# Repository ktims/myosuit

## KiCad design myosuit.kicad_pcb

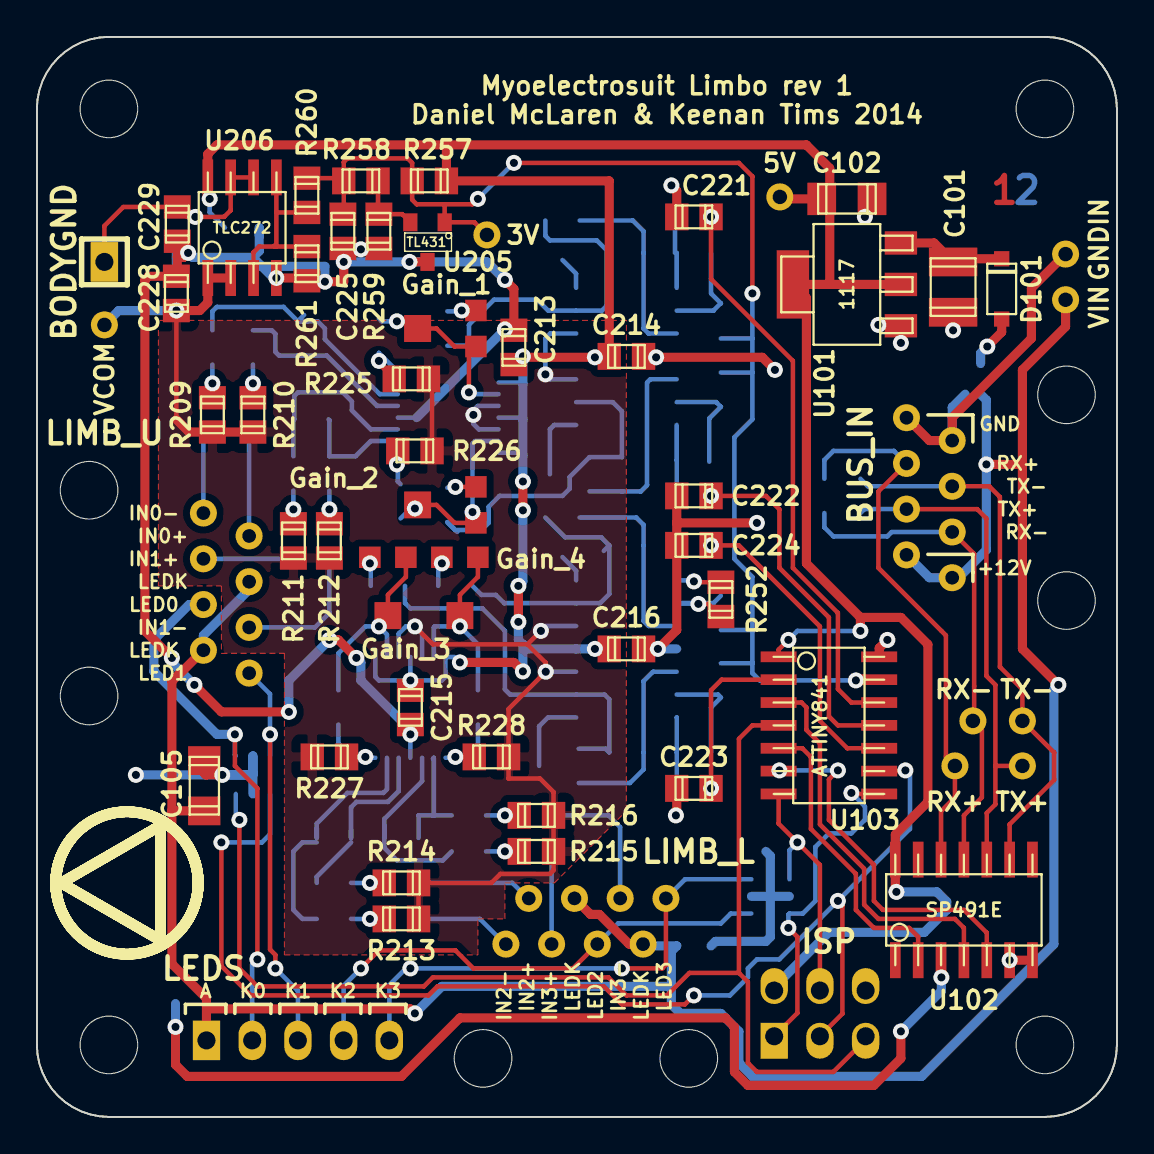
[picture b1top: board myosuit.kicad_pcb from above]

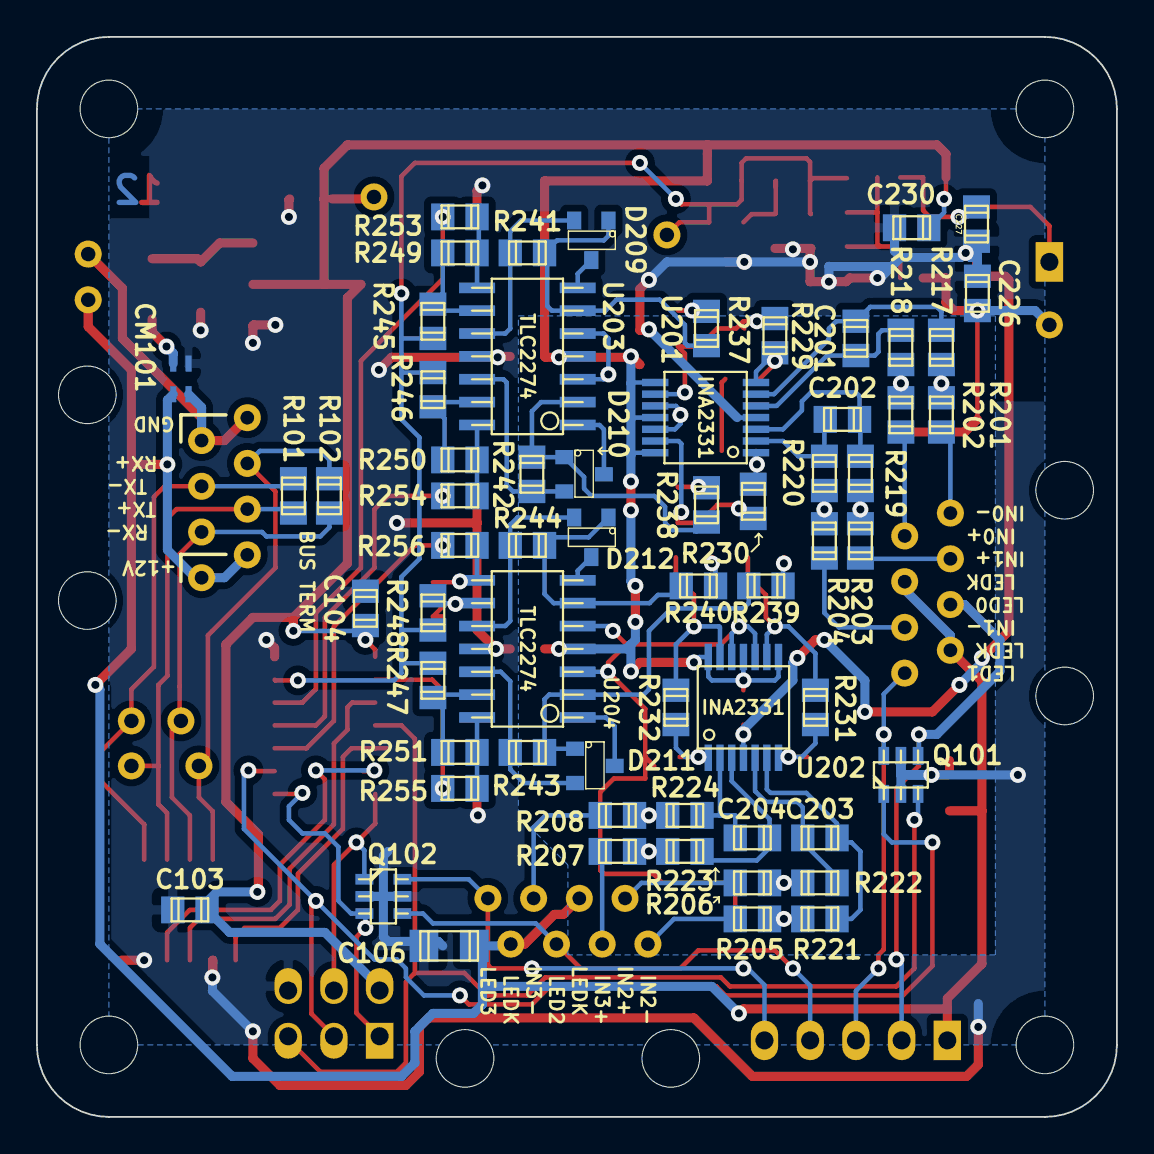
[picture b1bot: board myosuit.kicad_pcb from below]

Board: 2 copper layers, 60.0 x 60.0 mm, 123 parts (62 on the bottom side), 86 nets.

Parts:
C101: 47uF; c_1210
C102, C105, C106: 10uF; c_1206
C103, C104, C213, C214, C215, C216, C226, C227: 100nF; c_0805
C201, C202, C203, C204: 10nF; c_0805
C221, C222, C223, C224: 1u; c_0805
C225, C228, C229: 10u; c_0805
C230: 100n; c_0805
CM101: BOURNS-2012-CHOKE
D101: MBR0540; sod123
D209, D210, D211, D212: BAV199; SOT23
P101: LEDS; pin_strip_5-90
P102: ISP; pin_strip_3x2-90
P103: BUS_IN; FCI-shallow-rj45
P104: LIMB_U; FCI-shallow-rj45
P105: LIMB_L; FCI-shallow-rj45
P106: BODYGND; pin_strip_1
P107: VIN; Measurement_Point_Round-TH_Small
P108: GNDIN; Measurement_Point_Round-TH_Small
P109: TX+; Measurement_Point_Round-TH_Small
P110: 5V; Measurement_Point_Round-TH_Small
P111: RX+; Measurement_Point_Round-TH_Small
P112: RX-; Measurement_Point_Round-TH_Small
P113: TX-; Measurement_Point_Round-TH_Small
P201: 3V; Measurement_Point_Round-TH_Small
P202: VCOM; Measurement_Point_Round-TH_Small
Q101, Q102: FDC6305N; sot23-6
R101, R102: 120; r_0805
R201, R202, R203, R204, R205, R206, R207, R208, R217, R218, R219, R220, R221, R222, R223, R224, R258: 2k; r_0805
R209, R210, R211, R212, R213, R214, R215, R216: 3.3Meg; r_0805
R225, R226, R227, R228, R229, R230, R231, R232, R245, R246, R247, R248, R249, R250, R251, R252, R259: 10k; r_0805
R237, R238, R239, R240: 1k; r_0805
R241, R242, R243, R244, R260, R261: 100k; r_0805
R253, R254, R255, R256: 160; r_0805
R257: 330; r_0805
RV201: Gain_1; BOURNS-3303
RV202: Gain_2; BOURNS-3303
RV203: Gain_3; BOURNS-3303
RV204: Gain_4; BOURNS-3303
U101: 1117; sot223
U102: SP491E; so-14
U103: ATTINY841; so-14
U201, U202: INA2331; tssop-14
U203, U204: TLC2274; so-14
U205: TL431; SOT23
U206: TLC272; so-8
hole_3mm5, hole_3mm5#2, hole_3mm5#3, hole_3mm5#4: VAL**; hole_3mm5

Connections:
+3.3VADC: C225.1, P201.1, R245.1, R246.1, R247.1, R248.1, R257.2, R258.1, R260.1, U103.13, U205.1
+5V: C102.1, C103.1, C104.1, C213.2, C214.2, C215.2, C216.2, C230.2, P102.2, P110.1, R257.1, U101.2, U101.4, U102.14, U103.1, U201.8, U201.11, U201.14, U202.8, U202.11, U202.14, U203.4, U204.4, U206.8
/BUS_RX+: P103.6, P111.1, R102.2, U102.12
/BUS_RX-: P103.3, P112.1, R102.1, U102.11
/BUS_TX+: P103.4, P109.1, R101.1, U102.10
/BUS_TX-: P103.5, P113.1, R101.2, U102.9
/GNDIN: CM101.3, P103.7, P103.8, P108.1
/LED0: P101.2, P104.5, Q101.4
/LED1: P101.3, P104.8, Q101.6
/LED2: P101.4, P105.5, Q102.4
/LED3: P101.5, P105.8, Q102.6
/VIN: C105.1, C106.1, CM101.2, P101.1, P103.1, P103.2, P104.4, P104.7, P105.4, P105.7, P107.1
/analog input/BGND: C227.1, C229.1, P106.1, U206.6, U206.7
/analog input/IN0+: P104.2, R202.1
/analog input/IN0-: P104.1, R201.1
/analog input/IN1+: P104.3, R203.1
/analog input/IN1-: P104.6, R204.1
/analog input/IN2+: P105.2, R206.1
/analog input/IN2-: P105.1, R205.1
/analog input/IN3+: P105.3, R207.1
/analog input/IN3-: P105.6, R208.1
/analog input/OUT0: C221.1, R253.2, U103.12
/analog input/OUT1: C222.1, R254.2, U103.11
/analog input/OUT2: C223.1, R255.2, U103.2
/analog input/OUT3: C224.1, R256.2, U103.10
GND: C101.2, C102.2, C103.2, C104.2, C105.2, C106.2, C213.1, C214.1, C215.1, C216.1, C221.2, C222.2, C223.2, C224.2, C225.2, C226.2, C227.2, C228.2, C229.2, C230.1, CM101.4, P102.6, Q101.2, Q101.5, Q102.2, Q102.5, R259.2, R261.2, U101.1, U102.3, U102.6, U102.7, U103.14, U201.4, U202.4, U203.11, U204.11, U205.3, U206.4
unnamed: C101.1, D101.2, U101.3
unnamed: C201.1, R217.2, U201.6
unnamed: C201.2, R218.2, U201.5
unnamed: C202.1, R219.2, U201.3
unnamed: C202.2, R220.2, U201.2
unnamed: C203.1, R221.2, U202.6
unnamed: C203.2, R222.2, U202.5
unnamed: C204.1, R223.2, U202.3
unnamed: C204.2, R224.2, U202.2
unnamed: CM101.1, D101.1
unnamed: D209.1, R237.2, R241.1, U203.6
unnamed: D209.2, R241.2, U203.10
unnamed: D209.3, U203.7
unnamed: D210.1, R238.2, R242.1, U203.2
unnamed: D210.2, R242.2, U203.12
unnamed: D210.3, U203.1
unnamed: D211.1, R239.2, R243.1, U204.2
unnamed: D211.2, R243.2, U204.12
unnamed: D211.3, U204.1
unnamed: D212.1, R240.2, R244.1, U204.6
unnamed: D212.2, R244.2, U204.10
unnamed: D212.3, U204.7
unnamed: P102.1, Q102.3, U103.8
unnamed: P102.3, Q101.1, U103.9
unnamed: P102.4, Q102.1, U103.7
unnamed: P102.5, Q101.3, U103.4
unnamed: R201.2, R209.1, R217.1
unnamed: R202.2, R210.2, R218.1
unnamed: R203.2, R211.1, R219.1
unnamed: R204.2, R212.2, R220.1
unnamed: R205.2, R213.1, R221.1
unnamed: R206.2, R214.2, R222.1
unnamed: R207.2, R215.1, R223.1
unnamed: R208.2, R216.2, R224.1
unnamed: R225.2, R229.1, U201.7
unnamed: R226.2, R230.1, U201.1
unnamed: R227.2, R231.1, U202.7
unnamed: R228.2, R232.1, U202.1
unnamed: R229.2, RV201.1, RV201.2, U201.9
unnamed: R230.2, RV202.1, RV202.2, U201.13
unnamed: R231.2, RV203.1, RV203.2, U202.9
unnamed: R232.2, RV204.1, RV204.2, U202.13
unnamed: R237.1, RV201.3
unnamed: R238.1, RV202.3
unnamed: R239.1, RV203.3
unnamed: R240.1, RV204.3
unnamed: R245.2, R249.1, U203.9
unnamed: R246.2, R250.1, U203.13
unnamed: R247.2, R251.1, U204.13
unnamed: R248.2, R252.1, U204.9
unnamed: R249.2, R253.1, U203.8
unnamed: R250.2, R254.1, U203.14
unnamed: R251.2, R255.1, U204.14
unnamed: R252.2, R256.1, U204.8
unnamed: R258.2, R259.1, U205.2
unnamed: R260.2, R261.1, U206.3, U206.5
unnamed: U102.2, U103.5
unnamed: U102.4, U103.3
unnamed: U102.5, U103.6
VCOM: C226.1, C228.1, P202.1, R209.2, R210.1, R211.2, R212.1, R213.2, R214.1, R215.2, R216.1, R225.1, R226.1, R227.1, R228.1, U201.10, U201.12, U202.10, U202.12, U203.3, U203.5, U204.3, U204.5, U206.1, U206.2

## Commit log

2014-03-07 initial commit - rev1 boards
2014-03-16 add initial sourcecode
2014-03-17 work with dan on code
2014-05-27 work done with dan in March
2014-07-11 early implementation of command parser & usart input & adc - working remote led set via usart - working address set via usart - interrupt handling of ADC input works - sillier startup sequence
2014-07-13 more commands added, adc readable, osccal, work on bootloader, python test code
2014-07-14 Play with demo code
